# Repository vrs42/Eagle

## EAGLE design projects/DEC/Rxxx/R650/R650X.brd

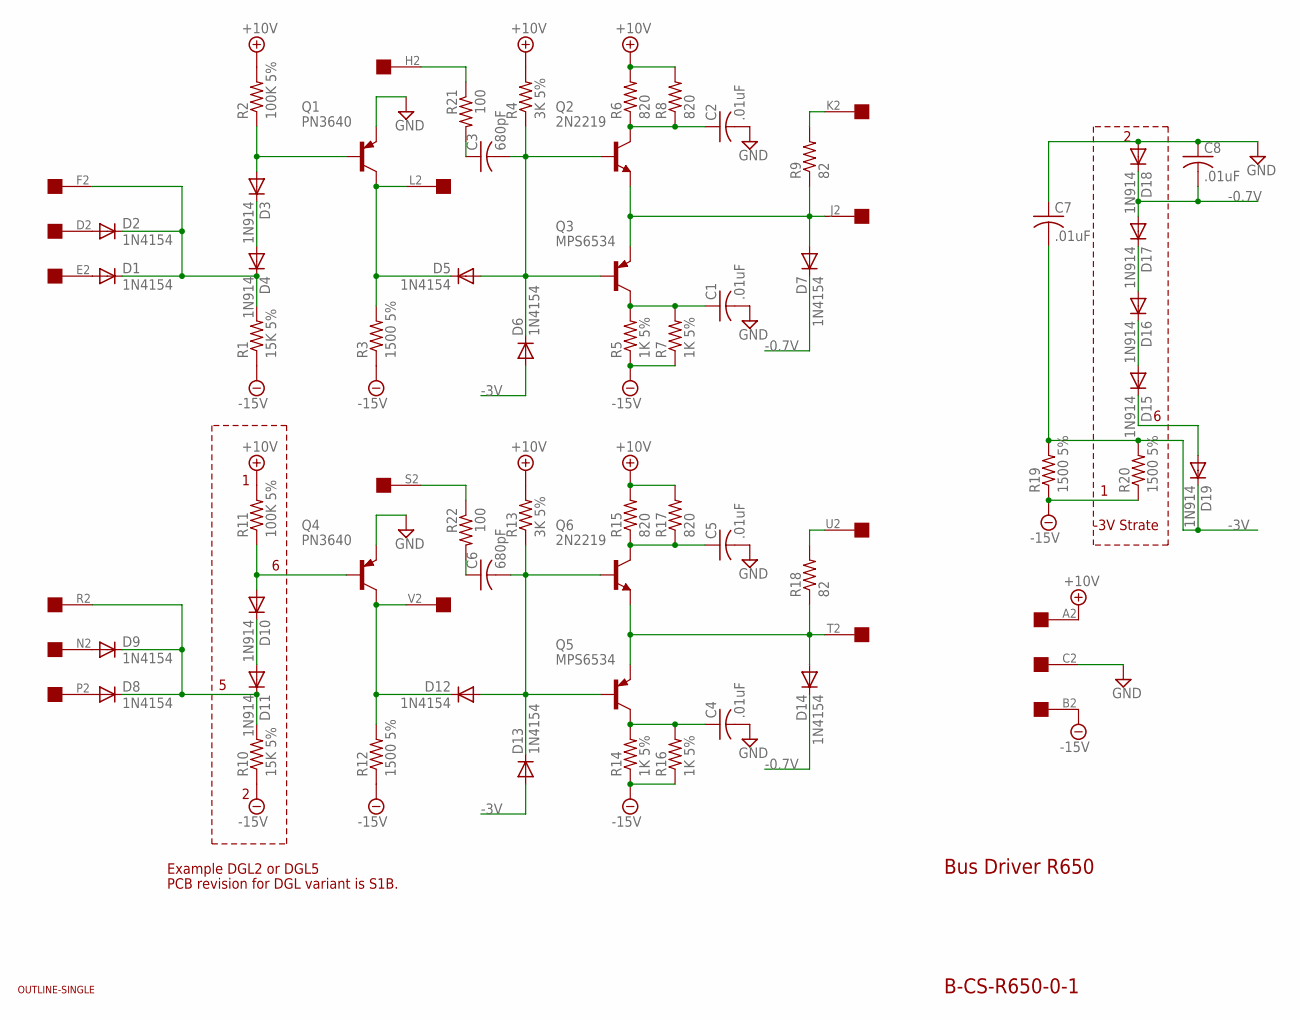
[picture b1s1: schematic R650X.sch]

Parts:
C1, C2, C4, C5, C7, C8: .01uF; C102-043X133
C3, C6: 680pF; C102-043X133
D1, D2, D5, D6, D7, D8, D9, D12, D13, D14: 1N4154; DO35-10
D3, D4, D10, D11, D15, D16, D17, D18, D19: 1N914; DO35-10
Q1, Q4: PN3640; TO39
Q2, Q6: 2N2219; TO5
Q3, Q5: MPS6534; TO39
R1, R10: 15K 5%; 0207/10
R2, R11: 100K 5%; 0207/10
R3, R12, R19, R20: 1500 5%; 0207/10
R4, R13: 3K 5%; 0207/10
R5, R7, R14, R16: 1K 5%; 0207/10
R6, R8, R15, R17: 820; 0207/10
R9, R18: 82; 0207/10
R21, R22: 100; 0207/10
U$1: OUTLINE-SINGLE; SINGLE
U$2: EDGE-1; EDGE-CON1

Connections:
+10V: R2.2, R4.2, R6.2, R8.2, R11.2, R13.2, R15.2, R17.2, U$2.A2
-0.7V: C8.2, D7.C, D14.C, D17.A, D18.C
-3V: C7.2, D6.A, D13.A, D19.C, R19.2, R20.2
-15V: R1.1, R3.1, R5.1, R7.1, R10.1, R12.1, R14.1, R16.1, R19.1, R20.1, U$2.B2
GND: C1.2, C2.2, C4.2, C5.2, C7.1, C8.1, D18.A, Q1.1 (E), Q4.1 (E), U$2.C2
unnamed: C3.2, D5.A, D6.C, Q2.2 (B), Q3.2 (B), R4.1
unnamed: D7.A, Q2.1 (E), Q3.1 (E), R9.1, U$2.J2
unnamed: R9.2, U$2.K2
unnamed: D5.C, Q1.3 (C), R3.2, U$2.L2
unnamed: C2.1, Q2.3 (C), R6.1, R8.1
unnamed: C1.1, Q3.3 (C), R5.2, R7.2
unnamed: D10.A, Q4.2 (B), R11.1
unnamed: D12.C, Q4.3 (C), R12.2, U$2.V2
unnamed: D8.C, D9.C, D11.C, R10.2, U$2.R2
unnamed: D10.C, D11.A
unnamed: D16.A, D17.C
unnamed: R21.1, U$2.H2
unnamed: C3.1, R21.2
unnamed: D15.A, D16.C
unnamed: C6.2, D12.A, D13.C, Q5.2 (B), Q6.2 (B), R13.1
unnamed: D14.A, Q5.1 (E), Q6.1 (E), R18.1, U$2.T2
unnamed: D3.A, Q1.2 (B), R2.1
unnamed: D1.A, U$2.E2
unnamed: D1.C, D2.C, D4.C, R1.2, U$2.F2
unnamed: D3.C, D4.A
unnamed: C5.1, Q6.3 (C), R15.1, R17.1
unnamed: C4.1, Q5.3 (C), R14.2, R16.2
unnamed: R18.2, U$2.U2
unnamed: R22.1, U$2.S2
unnamed: C6.1, R22.2
unnamed: D9.A, U$2.N2
unnamed: D8.A, U$2.P2
unnamed: D15.C, D19.A
unnamed: D2.A, U$2.D2

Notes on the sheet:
Bus Driver R650
B-CS-R650-0-1
-3V Strate
Example DGL2 or DGL5
PCB revision for DGL variant is S1B.

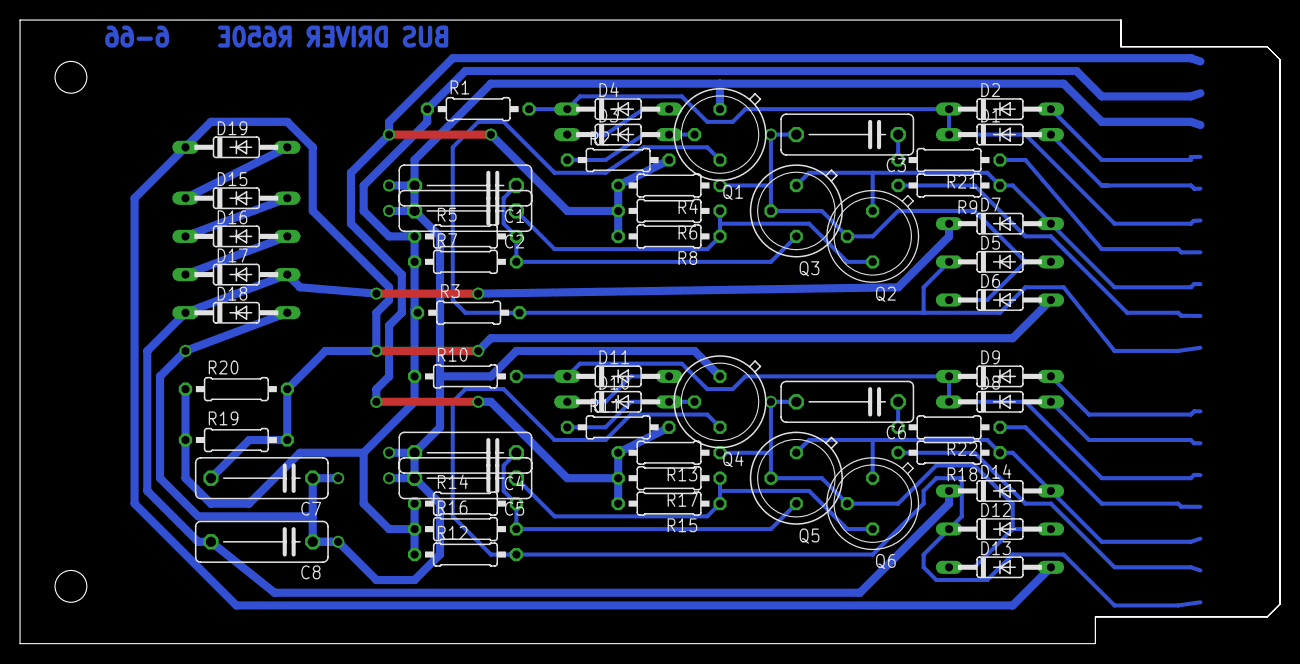
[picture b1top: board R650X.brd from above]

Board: 2 copper layers, 125.7 x 62.2 mm, 57 parts (0 on the bottom side), 34 nets.

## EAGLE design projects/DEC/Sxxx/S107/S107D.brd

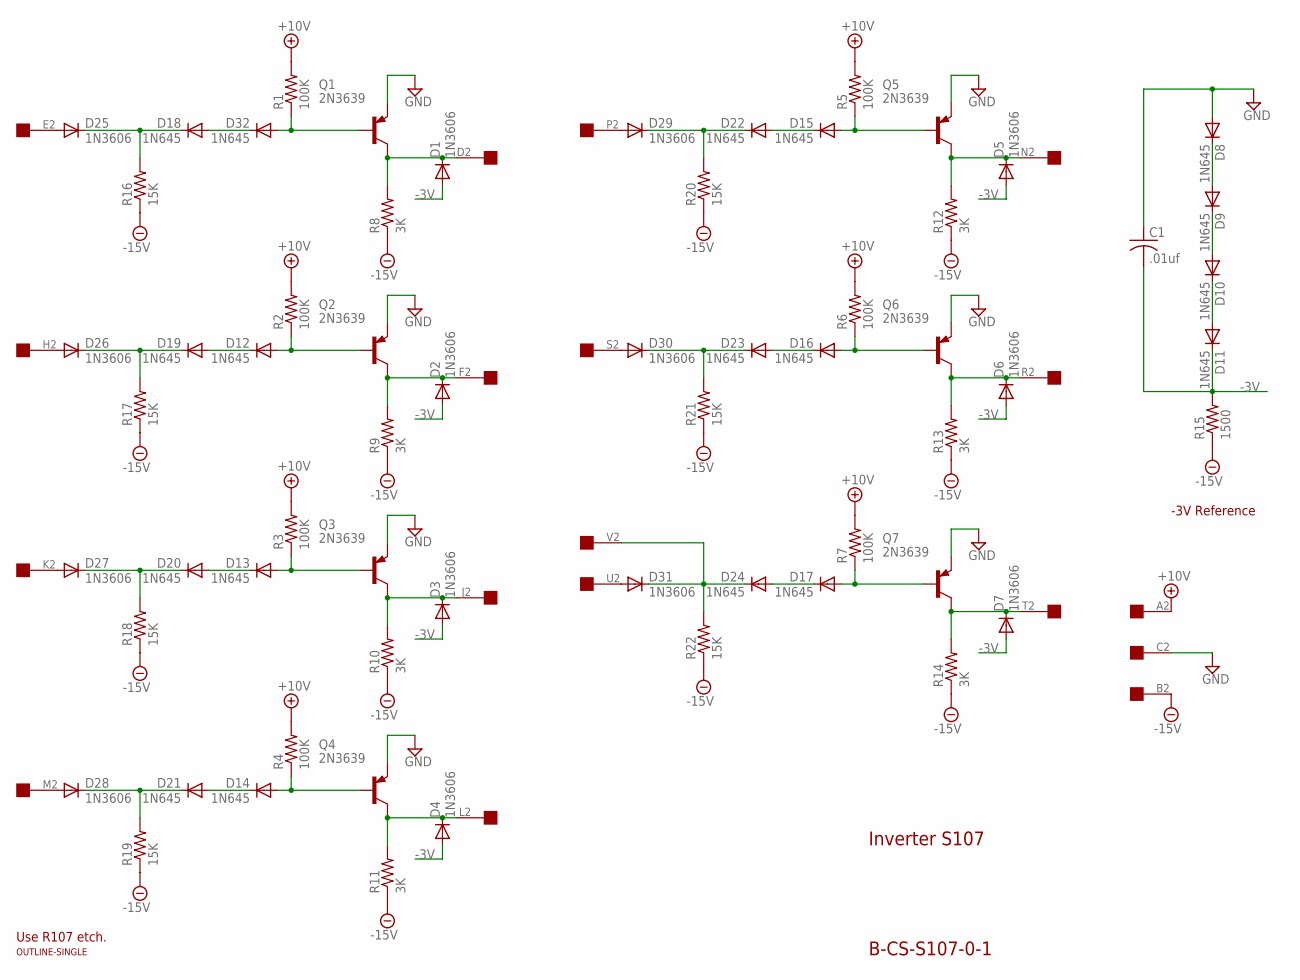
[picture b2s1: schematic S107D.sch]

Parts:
C1: .01uf; C050-025X075
D1, D2, D3, D4, D5, D6, D7, D25, D26, D27, D28, D29, D30, D31: 1N3606; DO35-10
D8, D9, D10, D11, D12, D13, D14, D15, D16, D17, D18, D19, D20, D21, D22, D23, D24, D32: 1N645; DO35-10
Q1, Q2, Q3, Q4, Q5, Q6, Q7: 2N3639; TO39
R1, R2, R3, R4, R5, R6, R7: 100K; 0207/10
R8, R9, R10, R11, R12, R13, R14: 3K; 0207/10
R15: 1500; 0207/10
R16, R17, R18, R19, R20, R21, R22: 15K; 0207/10
U$1: OUTLINE-SINGLE; SINGLE
U$2: EDGE-1; EDGE-CON1

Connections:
+10V: R1.2, R2.2, R3.2, R4.2, R5.2, R6.2, R7.2, U$2.A2
-3V: C1.2, D1.A, D2.A, D3.A, D4.A, D5.A, D6.A, D7.A, D11.C, R15.2
-15V: R8.1, R9.1, R10.1, R11.1, R12.1, R13.1, R14.1, R15.1, R16.1, R17.1, R18.1, R19.1, R20.1, R21.1, R22.1, U$2.B2
GND: C1.1, D8.A, Q1.1 (E), Q2.1 (E), Q3.1 (E), Q4.1 (E), Q5.1 (E), Q6.1 (E), Q7.1 (E), U$2.C2
unnamed: D7.C, Q7.3 (C), R14.2, U$2.T2
unnamed: D12.A, Q2.2 (B), R2.1
unnamed: D8.C, D9.A
unnamed: D2.C, Q2.3 (C), R9.2, U$2.F2
unnamed: D26.A, U$2.H2
unnamed: D19.C, D26.C, R17.2
unnamed: D12.C, D19.A
unnamed: D13.A, Q3.2 (B), R3.1
unnamed: D3.C, Q3.3 (C), R10.2, U$2.J2
unnamed: D27.A, U$2.K2
unnamed: D20.C, D27.C, R18.2
unnamed: D13.C, D20.A
unnamed: D9.C, D10.A
unnamed: D31.A, U$2.U2
unnamed: D17.A, Q7.2 (B), R7.1
unnamed: D10.C, D11.A
unnamed: D24.C, D31.C, R22.2, U$2.V2
unnamed: D17.C, D24.A
unnamed: D32.A, Q1.2 (B), R1.1
unnamed: D1.C, Q1.3 (C), R8.2, U$2.D2
unnamed: D25.A, U$2.E2
unnamed: D18.C, D25.C, R16.2
unnamed: D18.A, D32.C
unnamed: D14.A, Q4.2 (B), R4.1
unnamed: D4.C, Q4.3 (C), R11.2, U$2.L2
unnamed: D28.A, U$2.M2
unnamed: D21.C, D28.C, R19.2
unnamed: D14.C, D21.A
unnamed: D15.A, Q5.2 (B), R5.1
unnamed: D5.C, Q5.3 (C), R12.2, U$2.N2
unnamed: D29.A, U$2.P2
unnamed: D22.C, D29.C, R20.2
unnamed: D15.C, D22.A
unnamed: D16.A, Q6.2 (B), R6.1
unnamed: D6.C, Q6.3 (C), R13.2, U$2.R2
unnamed: D30.A, U$2.S2
unnamed: D23.C, D30.C, R21.2
unnamed: D16.C, D23.A

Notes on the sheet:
Inverter S107
B-CS-S107-0-1
-3V Reference
Use R107 etch.

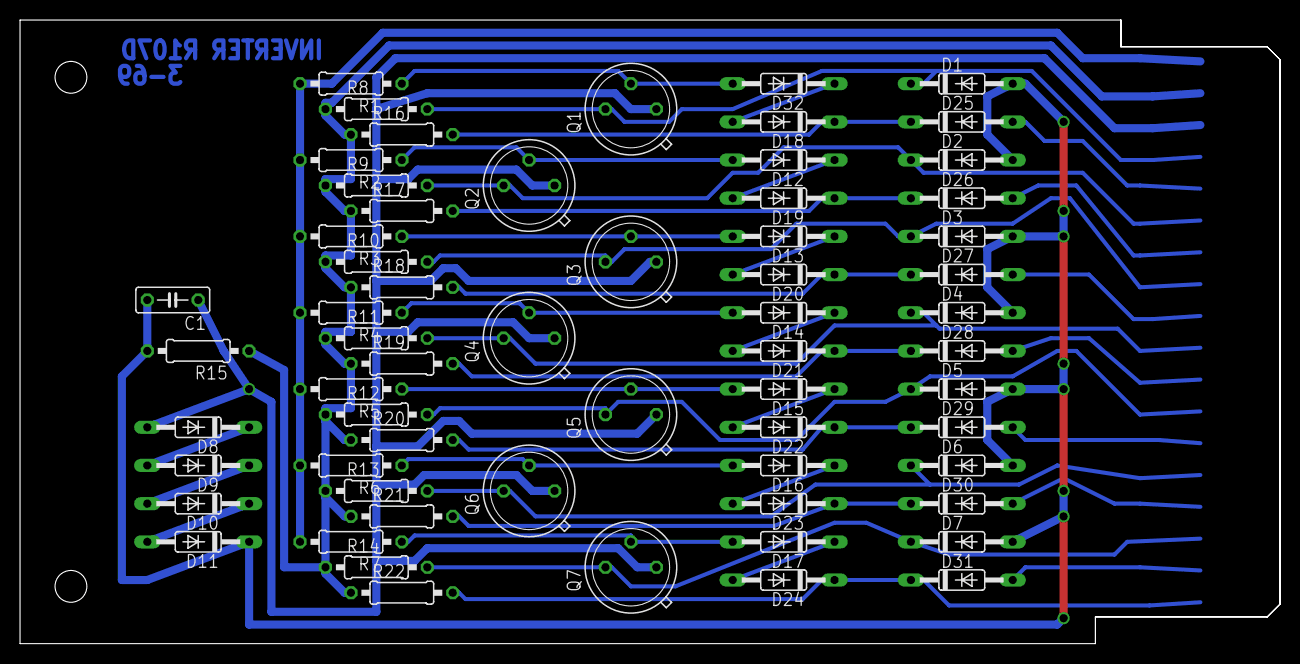
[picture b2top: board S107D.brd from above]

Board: 2 copper layers, 125.7 x 62.2 mm, 64 parts (0 on the bottom side), 42 nets.

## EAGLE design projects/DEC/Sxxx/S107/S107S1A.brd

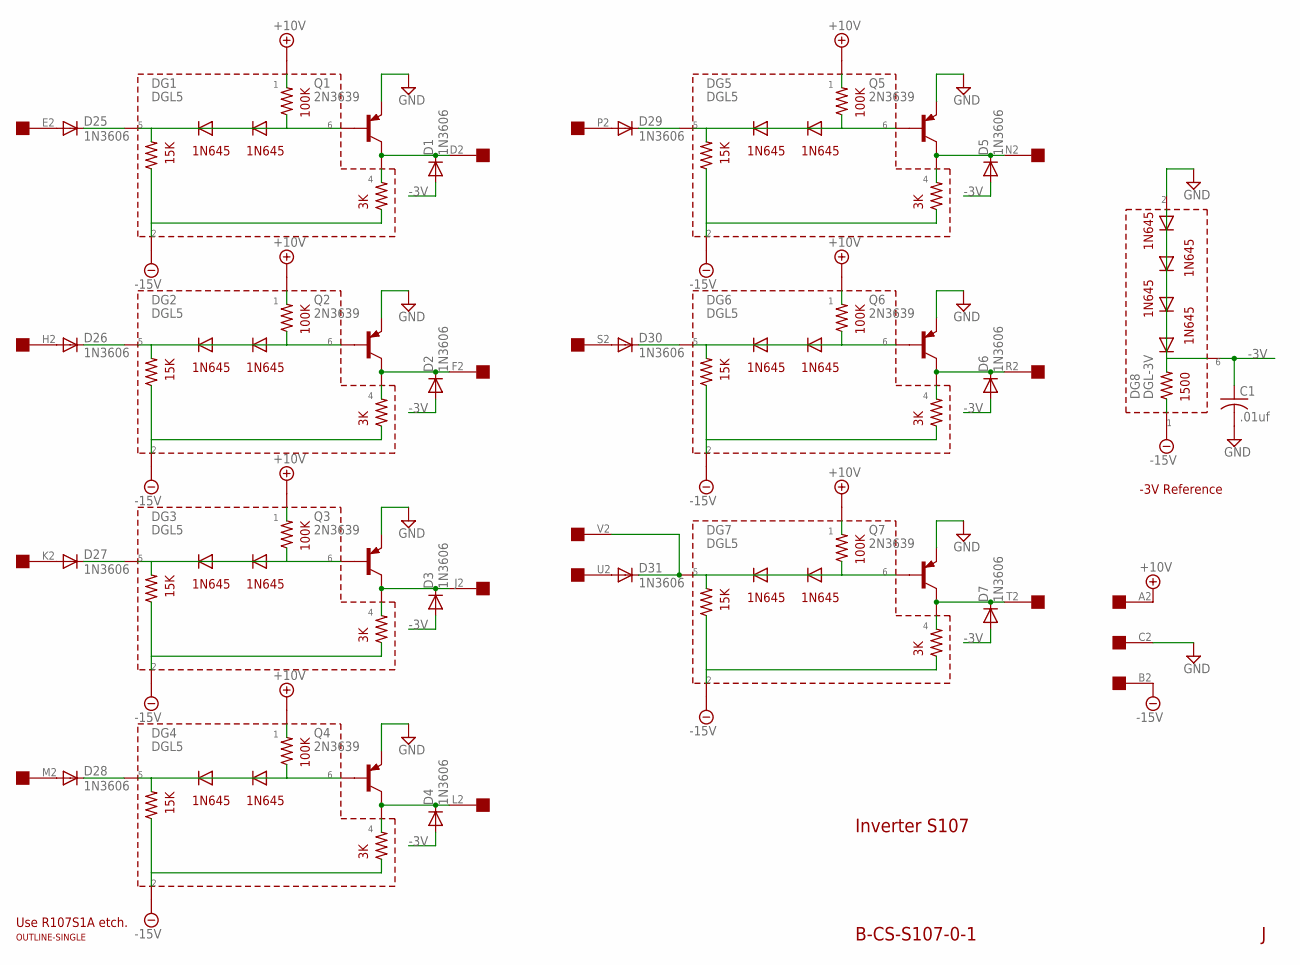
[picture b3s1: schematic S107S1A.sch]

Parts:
C1: .01uf; C050-025X075
D1, D2, D3, D4, D5, D6, D7, D25, D26, D27, D28, D29, D30, D31: 1N3606; DO35-10
DG1, DG2, DG3, DG4, DG5, DG6, DG7: DGL5; DGL2
DG8: DGL-3V; DGL2
Q1, Q2, Q3, Q4, Q5, Q6, Q7: 2N3639; TO39
U$1: OUTLINE-SINGLE; SINGLE
U$2: EDGE-1; EDGE-CON1

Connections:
+10V: DG1.P$1 (1), DG2.P$1 (1), DG3.P$1 (1), DG4.P$1 (1), DG5.P$1 (1), DG6.P$1 (1), DG7.P$1 (1), U$2.A2
-3V: C1.1, D1.A, D2.A, D3.A, D4.A, D5.A, D6.A, D7.A, DG8.P$6 (6)
-15V: DG1.P$2 (2), DG2.P$2 (2), DG3.P$2 (2), DG4.P$2 (2), DG5.P$2 (2), DG6.P$2 (2), DG7.P$2 (2), DG8.P$1 (1), U$2.B2
GND: C1.2, DG8.P$2 (2), Q1.1 (E), Q2.1 (E), Q3.1 (E), Q4.1 (E), Q5.1 (E), Q6.1 (E), Q7.1 (E), U$2.C2
unnamed: D7.C, DG7.P$4 (4), Q7.3 (C), U$2.T2
unnamed: DG2.P$6 (6), Q2.2 (B)
unnamed: D2.C, DG2.P$4 (4), Q2.3 (C), U$2.F2
unnamed: D26.A, U$2.H2
unnamed: DG3.P$6 (6), Q3.2 (B)
unnamed: DG4.P$6 (6), Q4.2 (B)
unnamed: D26.C, DG2.P$5 (5)
unnamed: D3.C, DG3.P$4 (4), Q3.3 (C), U$2.J2
unnamed: D27.A, U$2.K2
unnamed: D27.C, DG3.P$5 (5)
unnamed: D28.C, DG4.P$5 (5)
unnamed: D31.A, U$2.U2
unnamed: DG5.P$6 (6), Q5.2 (B)
unnamed: D31.C, DG7.P$5 (5), U$2.V2
unnamed: DG6.P$6 (6), Q6.2 (B)
unnamed: DG1.P$6 (6), Q1.2 (B)
unnamed: D1.C, DG1.P$4 (4), Q1.3 (C), U$2.D2
unnamed: D25.A, U$2.E2
unnamed: D25.C, DG1.P$5 (5)
unnamed: DG7.P$6 (6), Q7.2 (B)
unnamed: D30.C, DG6.P$5 (5)
unnamed: D4.C, DG4.P$4 (4), Q4.3 (C), U$2.L2
unnamed: D28.A, U$2.M2
unnamed: D5.C, DG5.P$4 (4), Q5.3 (C), U$2.N2
unnamed: D29.A, U$2.P2
unnamed: D29.C, DG5.P$5 (5)
unnamed: D6.C, DG6.P$4 (4), Q6.3 (C), U$2.R2
unnamed: D30.A, U$2.S2

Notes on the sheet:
Inverter S107
B-CS-S107-0-1
-3V Reference
Use R107S1A etch.

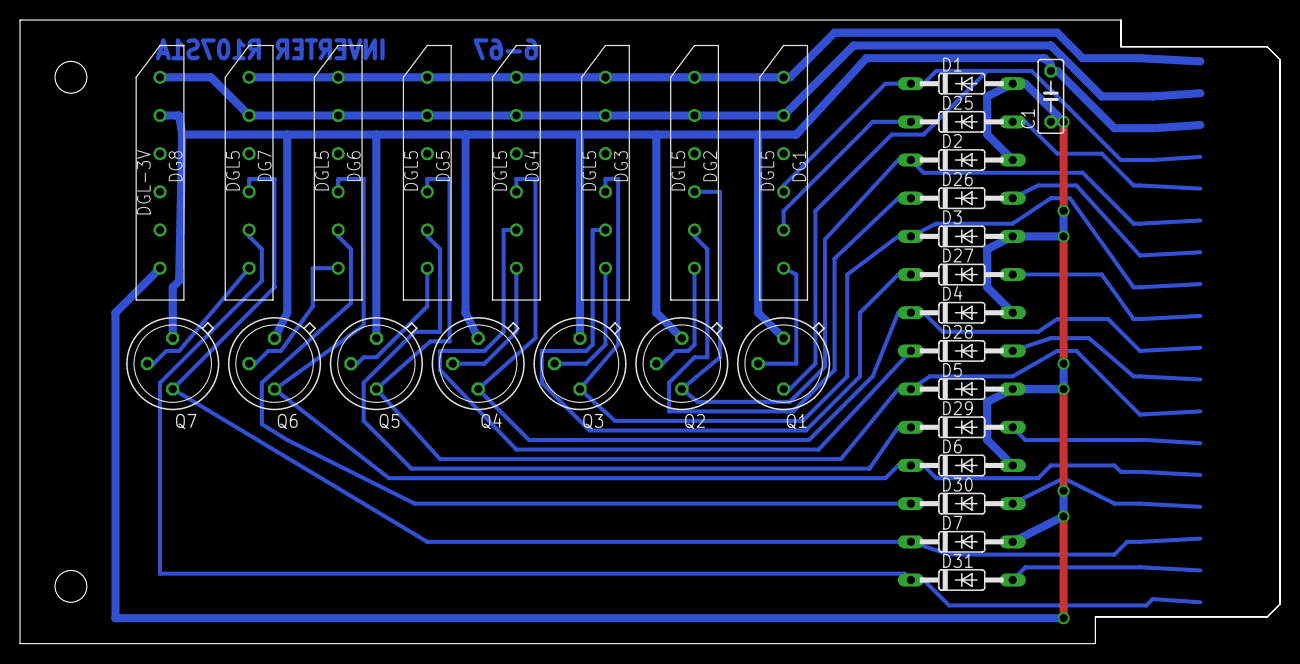
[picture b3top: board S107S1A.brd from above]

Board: 2 copper layers, 125.7 x 62.2 mm, 32 parts (0 on the bottom side), 32 nets.

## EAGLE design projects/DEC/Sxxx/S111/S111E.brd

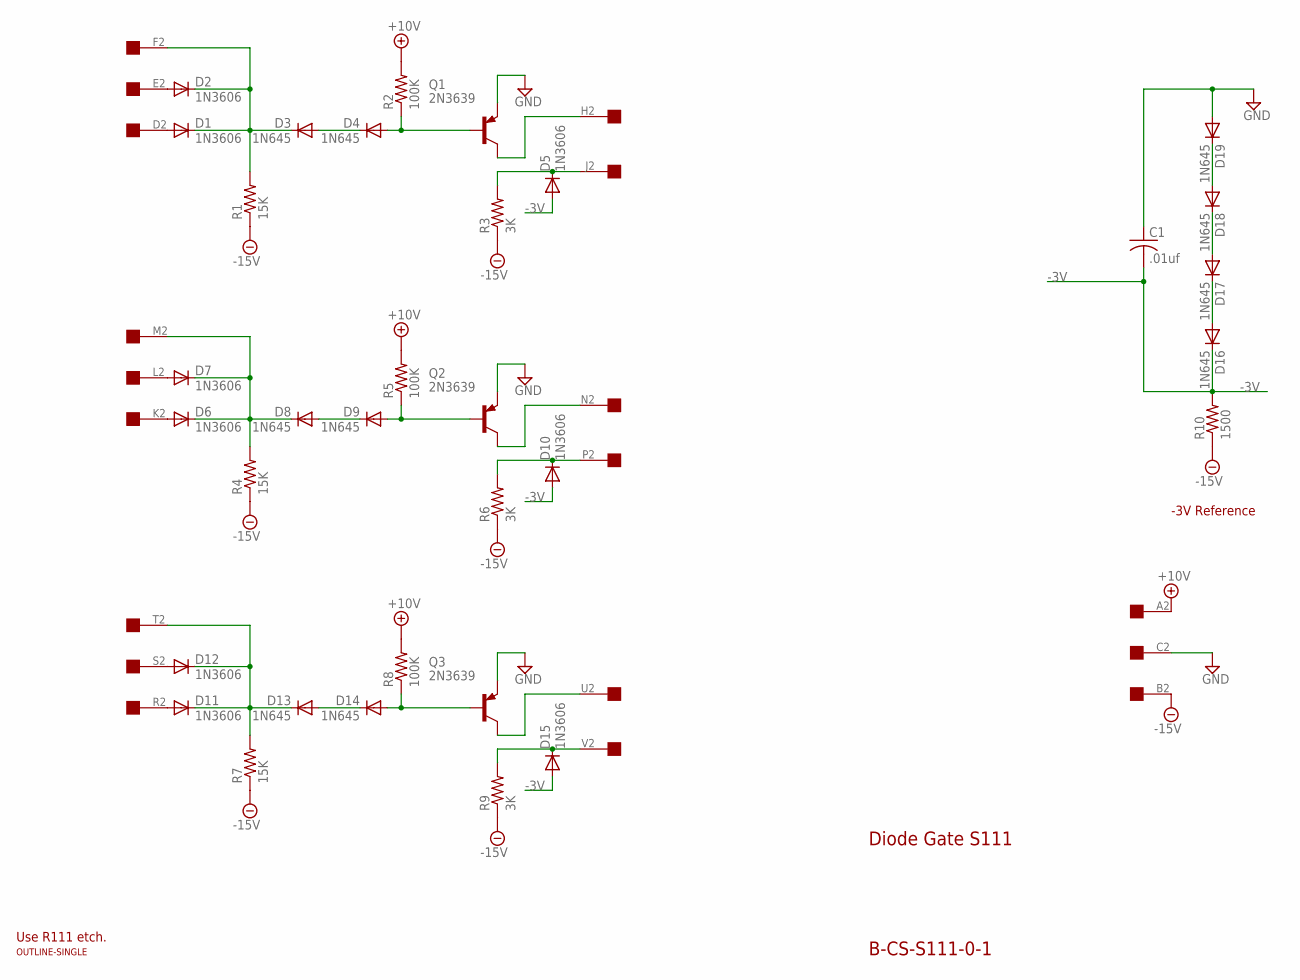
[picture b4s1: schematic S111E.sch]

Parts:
C1: .01uf; C050-025X075
D1, D2, D5, D6, D7, D10, D11, D12, D15: 1N3606; DO35-10
D3, D4, D8, D9, D13, D14, D16, D17, D18, D19: 1N645; DO35-10
Q1, Q2, Q3: 2N3639; TO39
R1, R4, R7: 15K; 0207/10
R2, R5, R8: 100K; 0207/10
R3, R6, R9: 3K; 0207/10
R10: 1500; 0207/10
U$1: OUTLINE-SINGLE; SINGLE
U$2: EDGE-1; EDGE-CON1

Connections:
+10V: R2.2, R5.2, R8.2, U$2.A2
-3V: C1.2, D5.A, D10.A, D15.A, D16.C, R10.2
-15V: R1.1, R3.1, R4.1, R6.1, R7.1, R9.1, R10.1, U$2.B2
GND: C1.1, D19.A, Q1.1 (E), Q2.1 (E), Q3.1 (E), U$2.C2
unnamed: D6.A, U$2.K2
unnamed: D9.A, Q2.2 (B), R5.1
unnamed: D18.A, D19.C
unnamed: D10.C, R6.2, U$2.P2
unnamed: Q1.3 (C), U$2.H2
unnamed: D6.C, D7.C, D8.C, R4.2, U$2.M2
unnamed: D8.A, D9.C
unnamed: D14.A, Q3.2 (B), R8.1
unnamed: D15.C, R9.2, U$2.V2
unnamed: D11.A, U$2.R2
unnamed: D11.C, D12.C, D13.C, R7.2, U$2.T2
unnamed: D13.A, D14.C
unnamed: D17.A, D18.C
unnamed: D7.A, U$2.L2
unnamed: Q2.3 (C), U$2.N2
unnamed: D16.A, D17.C
unnamed: Q3.3 (C), U$2.U2
unnamed: D4.A, Q1.2 (B), R2.1
unnamed: D5.C, R3.2, U$2.J2
unnamed: D1.A, U$2.D2
unnamed: D1.C, D2.C, D3.C, R1.2, U$2.F2
unnamed: D3.A, D4.C
unnamed: D12.A, U$2.S2
unnamed: D2.A, U$2.E2

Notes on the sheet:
Diode Gate S111
B-CS-S111-0-1
-3V Reference
Use R111 etch.

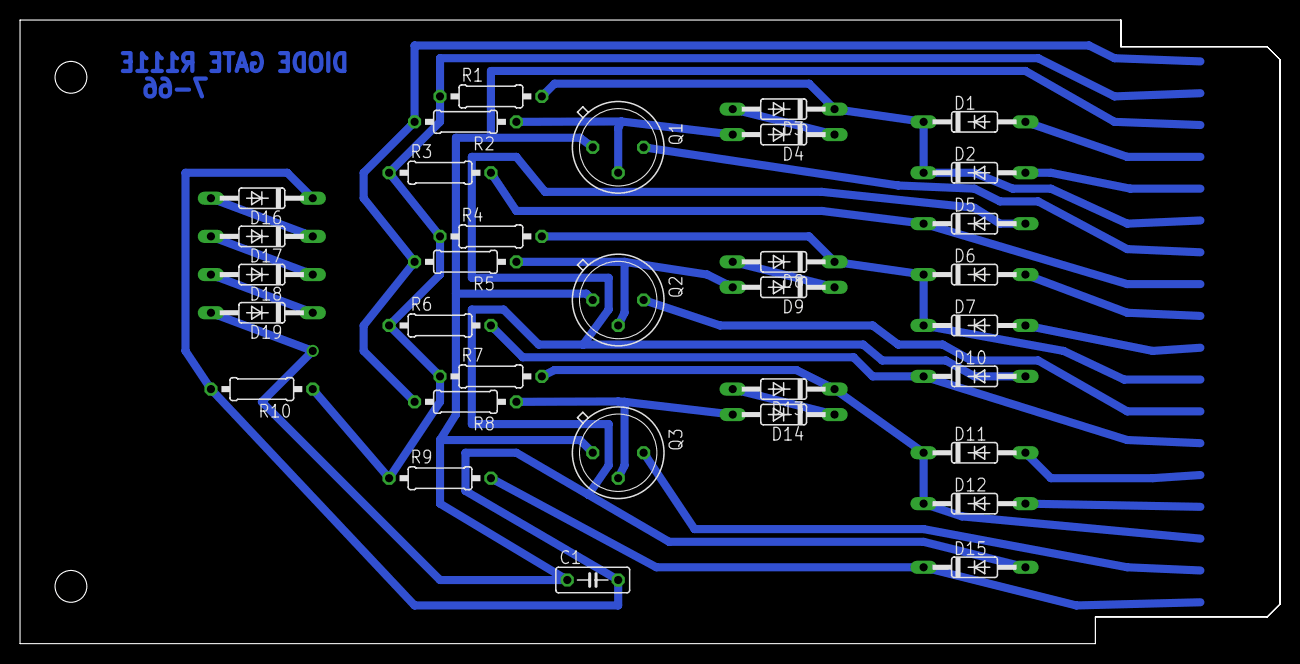
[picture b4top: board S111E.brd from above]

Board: 2 copper layers, 125.7 x 62.2 mm, 35 parts (0 on the bottom side), 28 nets.

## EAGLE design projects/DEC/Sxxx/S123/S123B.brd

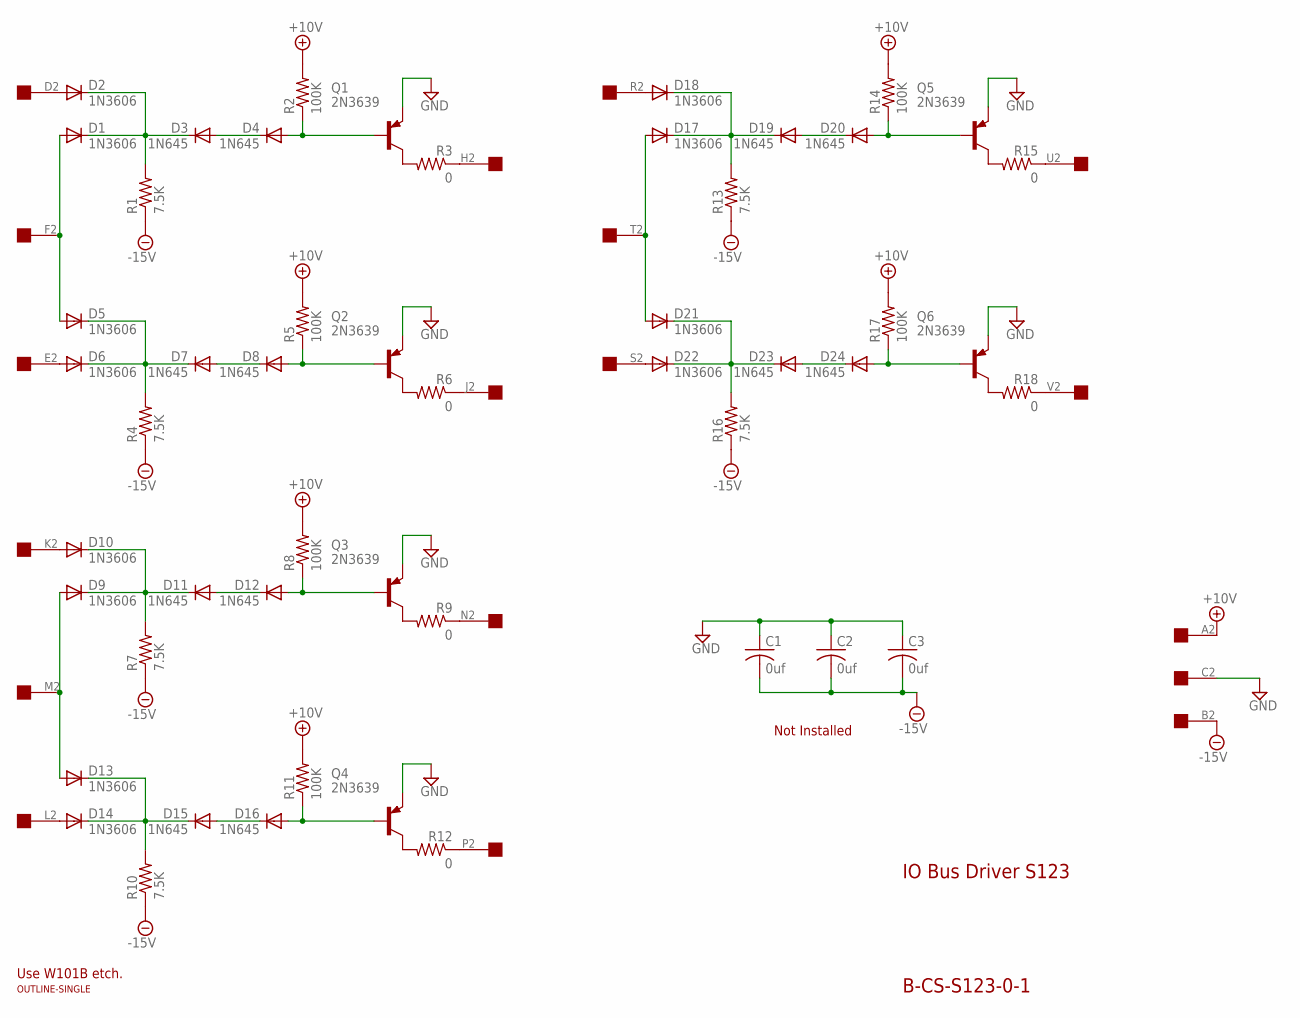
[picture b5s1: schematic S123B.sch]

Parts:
C1, C2, C3: 0uf; C050-025X075
D1, D2, D5, D6, D9, D10, D13, D14, D17, D18, D21, D22: 1N3606; DO35-10
D3, D4, D7, D8, D11, D12, D15, D16, D19, D20, D23, D24: 1N645; DO35-10
Q1, Q2, Q3, Q4, Q5, Q6: 2N3639; TO39
R1, R4, R7, R10, R13, R16: 7.5K; 0207/10
R2, R5, R8, R11, R14, R17: 100K; 0207/10
R3, R6, R9, R12, R15, R18: 0; 0207/10
U$1: OUTLINE-SINGLE; SINGLE
U$2: EDGE-1; EDGE-CON1

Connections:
+10V: R2.2, R5.2, R8.2, R11.2, R14.2, R17.2, U$2.A2
-15V: C1.2, C2.2, C3.2, R1.1, R4.1, R7.1, R10.1, R13.1, R16.1, U$2.B2
GND: C1.1, C2.1, C3.1, Q1.1 (E), Q2.1 (E), Q3.1 (E), Q4.1 (E), Q5.1 (E), Q6.1 (E), U$2.C2
unnamed: D2.A, U$2.D2
unnamed: D8.A, Q2.2 (B), R5.1
unnamed: R3.1, U$2.H2
unnamed: Q2.3 (C), R6.2
unnamed: D6.A, U$2.E2
unnamed: D5.C, D6.C, D7.C, R4.2
unnamed: D7.A, D8.C
unnamed: D12.A, Q3.2 (B), R8.1
unnamed: Q3.3 (C), R9.2
unnamed: D9.A, D13.A, U$2.M2
unnamed: D9.C, D10.C, D11.C, R7.2
unnamed: D11.A, D12.C
unnamed: R6.1, U$2.J2
unnamed: D10.A, U$2.K2
unnamed: R9.1, U$2.N2
unnamed: R12.1, U$2.P2
unnamed: D18.A, U$2.R2
unnamed: R15.1, U$2.U2
unnamed: D4.A, Q1.2 (B), R2.1
unnamed: Q1.3 (C), R3.2
unnamed: D1.A, D5.A, U$2.F2
unnamed: D1.C, D2.C, D3.C, R1.2
unnamed: D3.A, D4.C
unnamed: D16.A, Q4.2 (B), R11.1
unnamed: Q4.3 (C), R12.2
unnamed: D14.A, U$2.L2
unnamed: D13.C, D14.C, D15.C, R10.2
unnamed: D15.A, D16.C
unnamed: D20.A, Q5.2 (B), R14.1
unnamed: Q5.3 (C), R15.2
unnamed: D17.A, D21.A, U$2.T2
unnamed: D17.C, D18.C, D19.C, R13.2
unnamed: D19.A, D20.C
unnamed: D24.A, Q6.2 (B), R17.1
unnamed: Q6.3 (C), R18.2
unnamed: D22.A, U$2.S2
unnamed: D21.C, D22.C, D23.C, R16.2
unnamed: D23.A, D24.C
unnamed: R18.1, U$2.V2

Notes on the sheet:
IO Bus Driver S123
B-CS-S123-0-1
Not Installed
Use W101B etch.

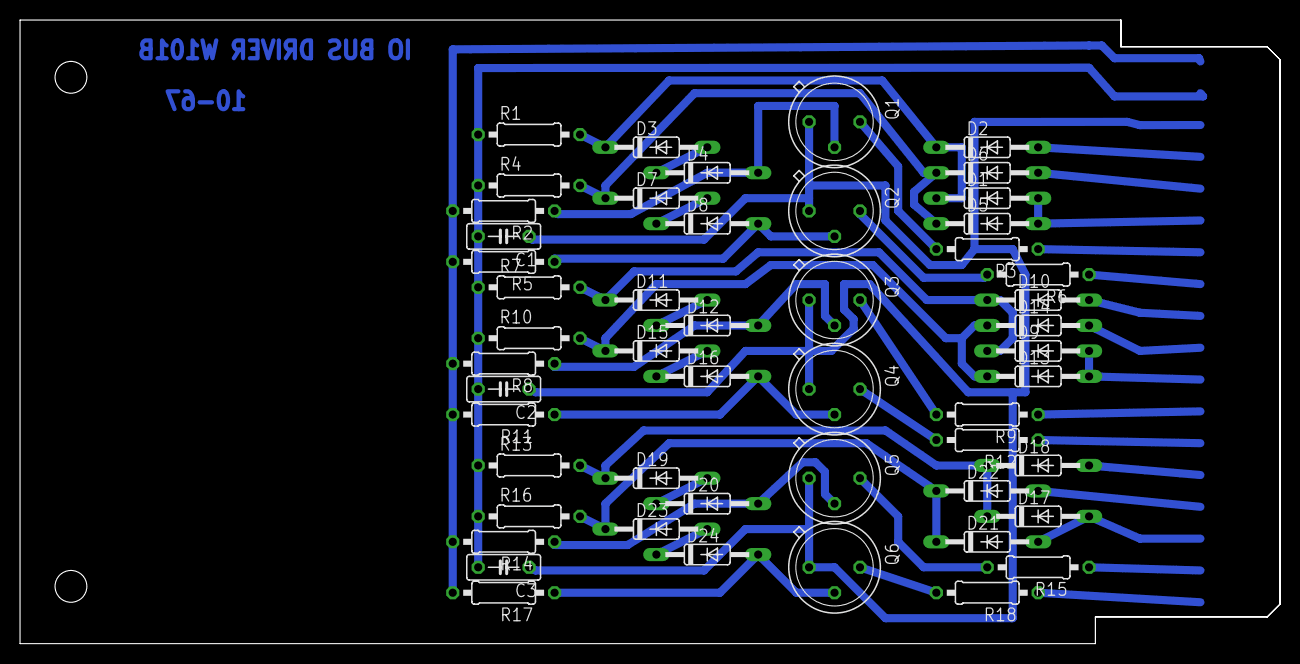
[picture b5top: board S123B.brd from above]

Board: 2 copper layers, 125.7 x 62.2 mm, 53 parts (0 on the bottom side), 42 nets.
